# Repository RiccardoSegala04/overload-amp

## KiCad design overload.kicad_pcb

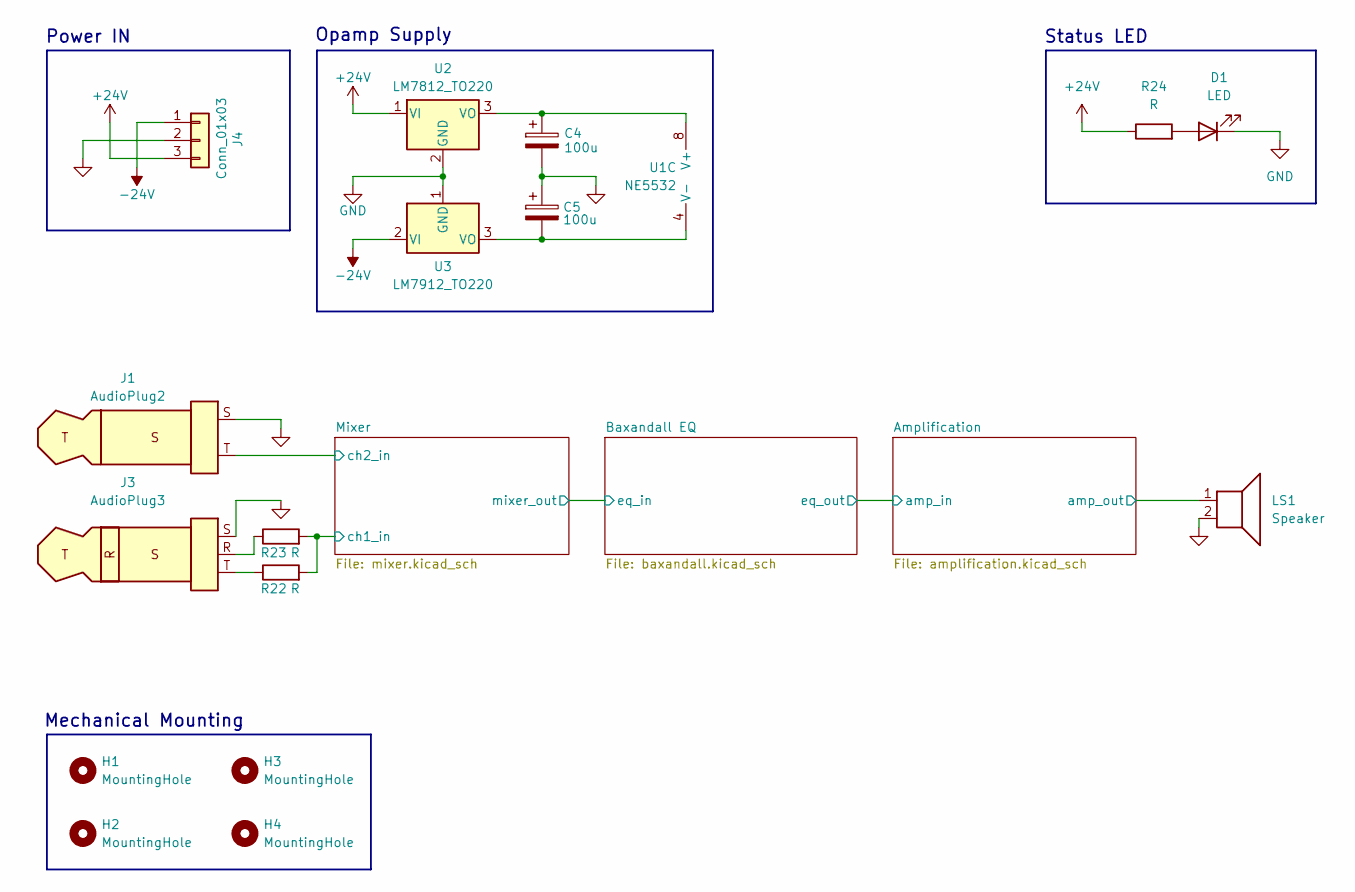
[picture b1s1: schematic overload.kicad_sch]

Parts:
C4, C5: 100u; CP_Radial_D6.3mm_P2.50mm
D1: LED; LED_D5.0mm
H1, H2, H3, H4: MountingHole; MountingHole_4.3mm_M4
J1: AudioPlug2; TRS
J3: AudioPlug3; 325 jack
J4: Conn_01x03; TerminalBlock_MaiXu_MX126-5.0-03P_1x03_P5.00mm
LS1: Speaker; TerminalBlock_MaiXu_MX126-5.0-02P_1x02_P5.00mm
R22, R23, R24: R; R_Axial_DIN0207_L6.3mm_D2.5mm_P7.62mm_Horizontal
U1: NE5532; DIP-8_W7.62mm_Socket
U2: LM7812_TO220; TO-220-3_Vertical
U3: LM7912_TO220; TO-220-3_Vertical

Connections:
+24V: J4.3, R24.1, U2.1 (VI); also elsewhere on the board
-24V: J4.1, U3.2 (VI); also elsewhere on the board
/Amplification/amp_out_fb: LS1.1; also elsewhere on the board
/Mixer/ch1_in: R22.2, R23.2; also elsewhere on the board
/Mixer/ch2_in: J1.T; also elsewhere on the board
GND: C4.2, C5.1, D1.1 (K), J1.S, J3.S, J4.2, LS1.2, U2.2 (GND), U3.1 (GND); also elsewhere on the board
unnamed: D1.2 (A), R24.2
unnamed: J3.R, R23.1
unnamed: J3.T, R22.1
unnamed: C4.1, U1.8 (V+), U2.3 (VO)
unnamed: C5.2, U1.4 (V-), U3.3 (VO)

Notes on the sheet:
Status LED
Mechanical Mounting
Power IN
Opamp Supply

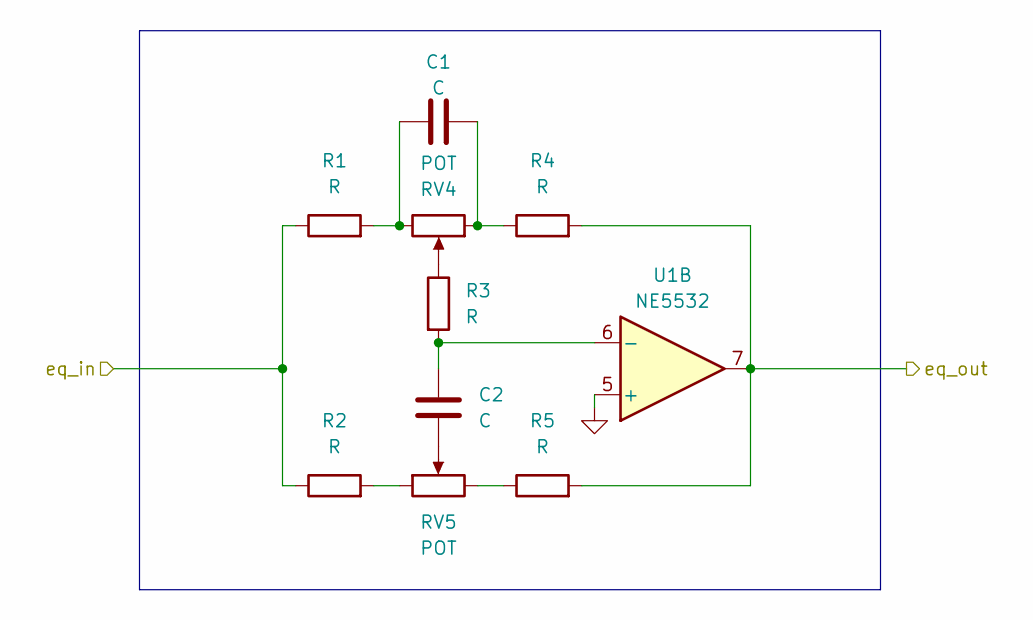
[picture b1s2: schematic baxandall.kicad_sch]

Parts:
C1, C2: C; C_Disc_D5.0mm_W2.5mm_P5.00mm
R1, R2, R3, R4, R5: R; R_Axial_DIN0207_L6.3mm_D2.5mm_P7.62mm_Horizontal
RV4, RV5: POT; Potentiometer_Alps_RK163_Single_Horizontal
U1: NE5532; DIP-8_W7.62mm_Socket

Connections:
/Amplification/amp_in: R4.2, R5.2, U1.7; also elsewhere on the board
/Baxandall EQ/eq_in: R1.1, R2.1; also elsewhere on the board
GND: U1.5 (+); also elsewhere on the board
unnamed: C1.1, R1.2, RV4.3
unnamed: C1.2, R4.1, RV4.1
unnamed: C2.1, RV5.2
unnamed: R2.2, RV5.1
unnamed: R3.1, RV4.2
unnamed: R5.1, RV5.3
unnamed: C2.2, R3.2, U1.6 (-)

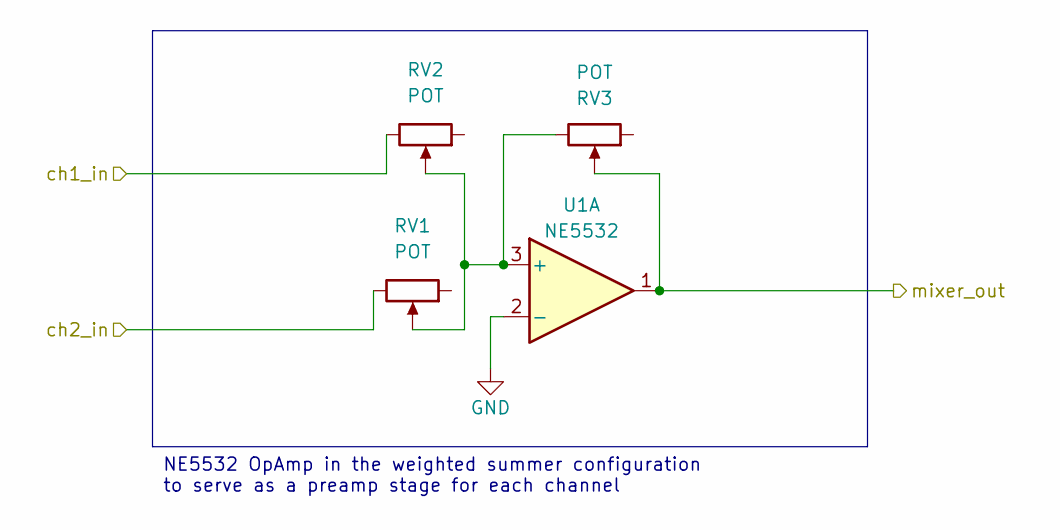
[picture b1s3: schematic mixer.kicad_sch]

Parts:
RV1, RV2, RV3: POT; Potentiometer_Alps_RK163_Single_Horizontal
U1: NE5532; DIP-8_W7.62mm_Socket

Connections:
/Baxandall EQ/eq_in: RV3.2, U1.1; also elsewhere on the board
/Mixer/ch1_in: RV2.3; also elsewhere on the board
/Mixer/ch2_in: RV1.3; also elsewhere on the board
GND: U1.2 (-); also elsewhere on the board
unnamed: RV1.2, RV2.2, RV3.3, U1.3 (+)

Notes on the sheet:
NE5532 OpAmp in the weighted summer configuration to serve as a preamp stage for each channel

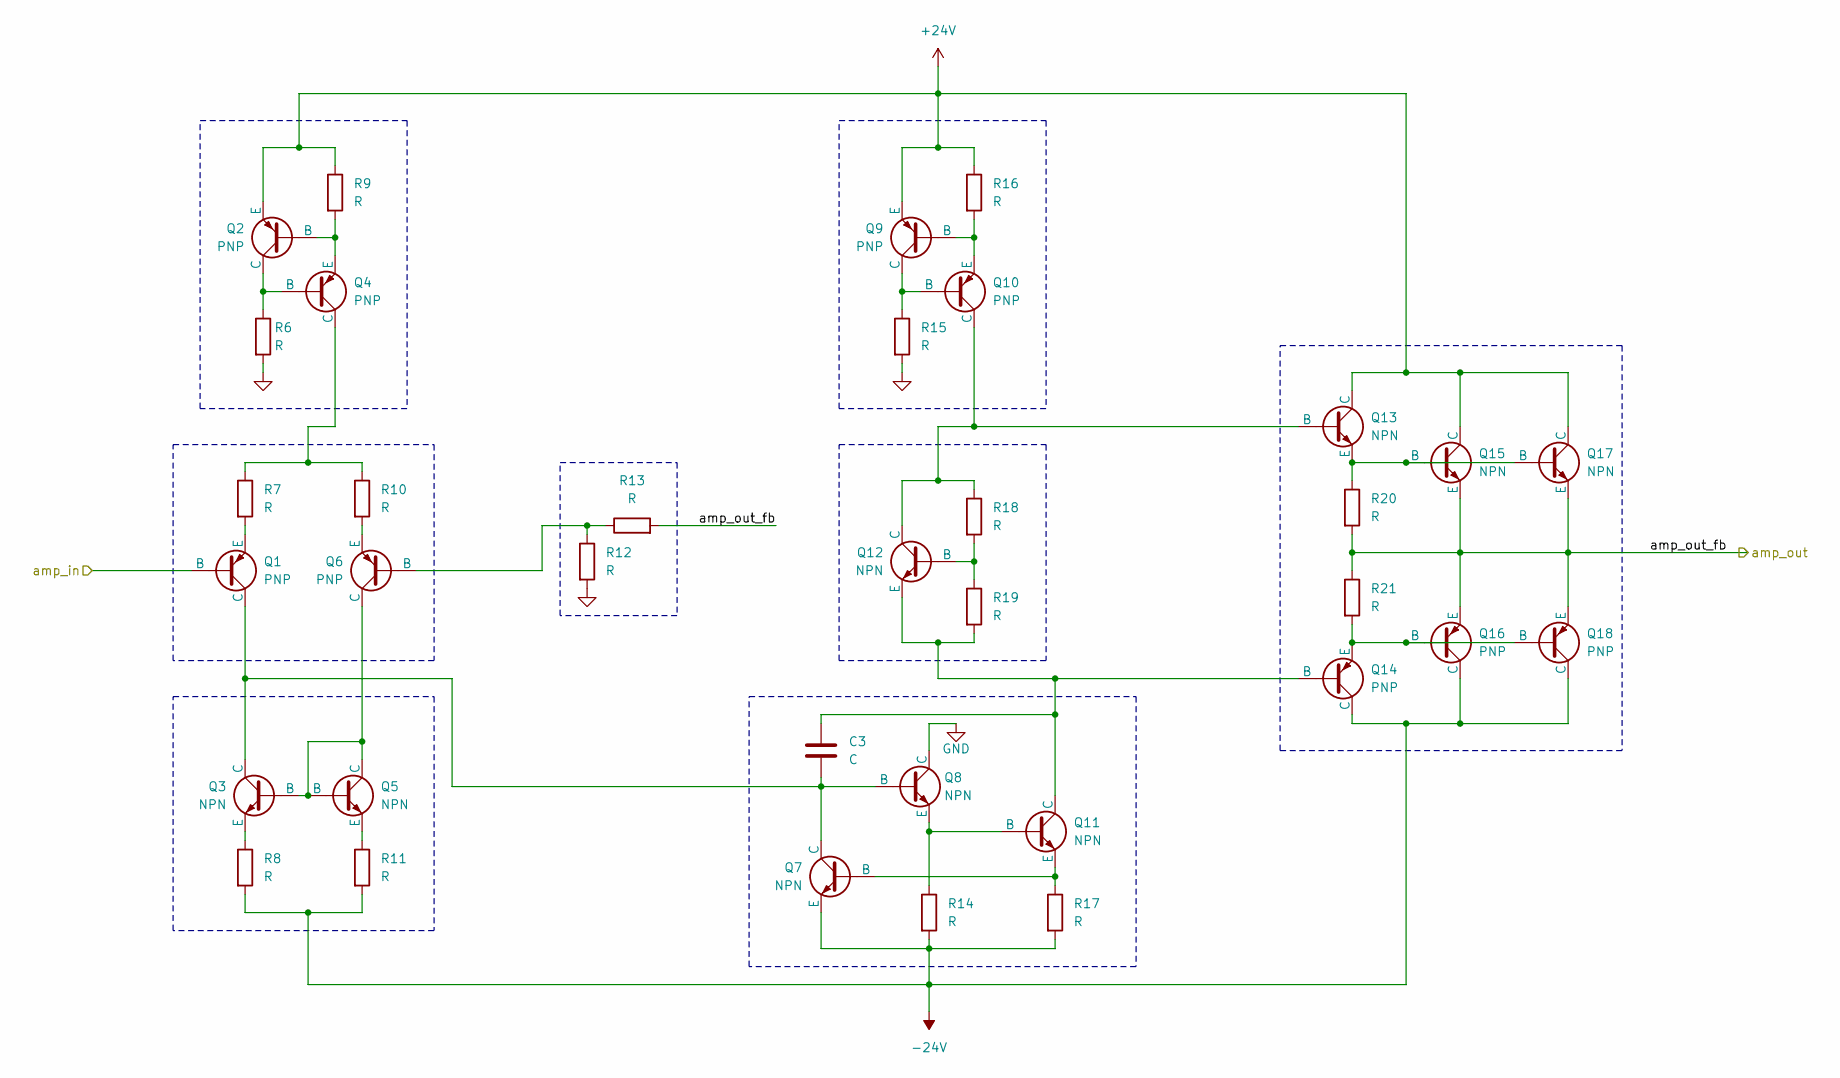
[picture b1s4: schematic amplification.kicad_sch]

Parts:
C3: C; C_Disc_D5.0mm_W2.5mm_P5.00mm
Q1, Q2, Q4, Q6, Q9, Q10, Q14: PNP; P210_TO-92
Q3, Q5, Q7, Q8, Q11, Q12, Q13: NPN; P210_TO-92
Q15, Q17: NPN; TO-220_STM
Q16, Q18: PNP; TO-220_STM
R6, R7, R8, R9, R10, R11, R12, R13, R14, R15, R16, R17, R18, R19, R20, R21: R; R_Axial_DIN0207_L6.3mm_D2.5mm_P7.62mm_Horizontal

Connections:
+24V: Q2.3 (E), Q9.3 (E), Q13.1 (C), Q15.1 (C), Q17.1 (C), R9.1, R16.1; also elsewhere on the board
-24V: Q7.3 (E), Q14.1 (C), Q16.1 (C), Q18.1 (C), R8.2, R11.2, R14.2, R17.2; also elsewhere on the board
/Amplification/amp_in: Q1.2 (B); also elsewhere on the board
/Amplification/amp_out_fb: Q15.3 (E), Q16.3 (E), Q17.3 (E), Q18.3 (E), R13.2, R20.2, R21.1; also elsewhere on the board
GND: Q8.1 (C), R6.2, R12.2, R15.2; also elsewhere on the board
unnamed: C3.2, Q1.1 (C), Q3.1 (C), Q7.1 (C), Q8.2 (B)
unnamed: Q1.3 (E), R7.2
unnamed: Q2.2 (B), Q4.3 (E), R9.2
unnamed: Q2.1 (C), Q4.2 (B), R6.1
unnamed: Q3.2 (B), Q5.1 (C), Q5.2 (B), Q6.1 (C)
unnamed: Q3.3 (E), R8.1
unnamed: Q4.1 (C), R7.1, R10.1
unnamed: Q5.3 (E), R11.1
unnamed: Q6.2 (B), R12.1, R13.1
unnamed: Q6.3 (E), R10.2
unnamed: Q9.1 (C), Q10.2 (B), R15.1
unnamed: Q10.1 (C), Q12.1 (C), Q13.2 (B), R18.1
unnamed: Q9.2 (B), Q10.3 (E), R16.2
unnamed: Q8.3 (E), Q11.2 (B), R14.1
unnamed: C3.1, Q11.1 (C), Q12.3 (E), Q14.2 (B), R19.2
unnamed: Q7.2 (B), Q11.3 (E), R17.1
unnamed: Q12.2 (B), R18.2, R19.1
unnamed: Q13.3 (E), Q15.2 (B), Q17.2 (B), R20.1
unnamed: Q14.3 (E), Q16.2 (B), Q18.2 (B), R21.2

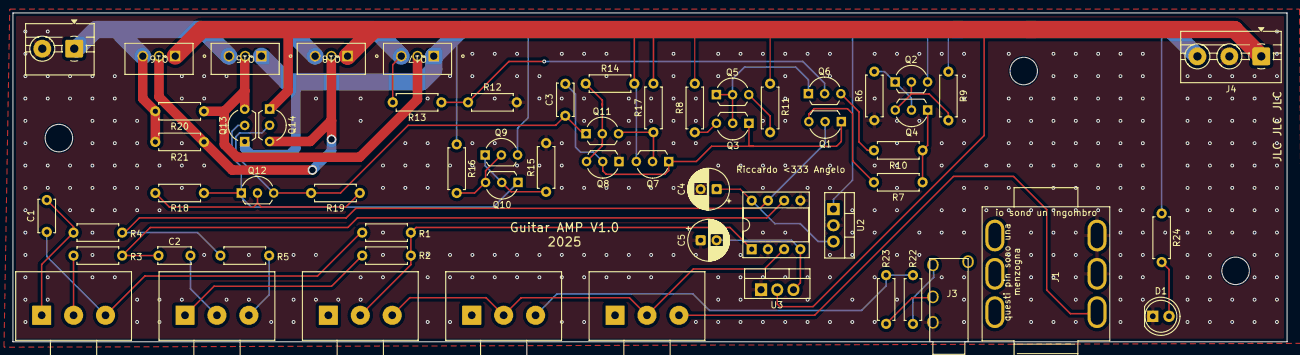
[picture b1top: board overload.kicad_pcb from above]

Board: 2 copper layers, 199.5 x 51.5 mm, 63 parts (0 on the bottom side), 40 nets.

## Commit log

2025-08-03 inital commit
2025-08-03 feat: added gitignore
2025-08-03 initial schematics
2025-08-04 feat: added NE5532DR footprint
2025-08-04 feat: updated footprint tables
2025-09-07 add spice simulation of amp
2025-09-07 organize the schematic and add status led
2025-09-07 add gnd to audio jacks
2025-09-08 organize amp sheet
2025-09-11 add output stage parallelism and miller capacitor
2025-09-18 initial component placement in pcb
2025-09-29 feat: added potentiometes footprint
2025-09-29 feat: added potentiometes to pcb
2025-09-29 feat: added custom TRS library and updated lib table
2025-09-29 feat: updated schematic
2025-09-29 initial routing
2025-09-29 hell yea, angelo do your magic
2025-09-29 fix: custom TRS pin netclasses
2025-09-29 route bjt amplifier stage
2025-09-29 fix lololol
2025-09-29 make power bus straighter
2025-09-29 feat: added 3.5 tht jack custom lib
2025-09-29 feat: assigned footprint to symb
2025-09-29 feat: added 3.5 jack to pcb
2025-10-25 RAAAAH Let's gooo to production baby
2025-11-12 remove mask on high current tracks
